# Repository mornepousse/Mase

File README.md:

# Mase
 Custom esp32 mouse.
 
 |index|References|Value|Footprint|Quantity|
 |:-|:--------|:-|:--|:-|
|1| C101, C102, C106, C108, C110    |0.1u|C_0805_2012Metric|5|
|2| C103, C105, C107, C109, C111    |1u|C_0805_2012Metric|5|
|3| C104                            |4.7u|C_0805_2012Metric     |1|
|4| R102, R103, R104                |10k|R_0805_2012Metric|3|
|5| R107, R108, R109                |?|R_0805_2012Metric|3|
|6| R105, R106                      |R_1206|R_0805_2012Metric|2|
|7| R101|39|R_0805_2012Metric|1|
|8| D101, D102|LED_3mm|LED_D3.0mm|2|
|9| U1|ESP32-S3-WROOM-1|ESP32-S3-WROOM-1|1|
|10|U2|PMW3360|PMW3360|1|
|11|U4|	TLV73333PDBV|	SOT-23-5	|1|
|12|U103|	TCR2EF19|	SOT-23-5	|1|
|13|SW1, SW2|	Push_Button|	SW_Hotswap_Kailh_Choc_V1V2_1.00u	|2|
|14|SW101, SW104|	Push_Button|	SW_Micro_Switch	|2|
|15|SW103, SW106|	Push_Button|	SW_Push_1P1T_NO_CK_KSC7xxJ	|2|
|16|SW3|	RotaryEncoder_Switch_MP|	RollerEncoder_Panasonic_EVQWGD001	|1|
|17|	SW102|	Push_Button|Switch_Toggle_SPDT_SubMini	|1|
|18|TP101, TP102, TP103, TP104, TP105, TP106, TP107|TestPoint|TestPoint_Pad_D1.0mm|7|
|19|	H1, H2, H3, H4|	MountingHole|MountingHole_3.2mm_M3|4|
|20|	Brd101|	SSD1306|	128x64OLED	|1|
|21|	J1|	Conn_01x04|	PinHeader_1x04_P2.54mm_Vertical	|1|
|22|	J2|	Conn_02x04_Counter_Clockwise|IDC-Header_2x04_P2.54mm_Vertical|1|
|23|	J101|	Conn_02x03_Counter_Clockwise|	Harwin_Gecko-G125-FVX0605L0X_2x03_P1.25mm_Vertical	|1|

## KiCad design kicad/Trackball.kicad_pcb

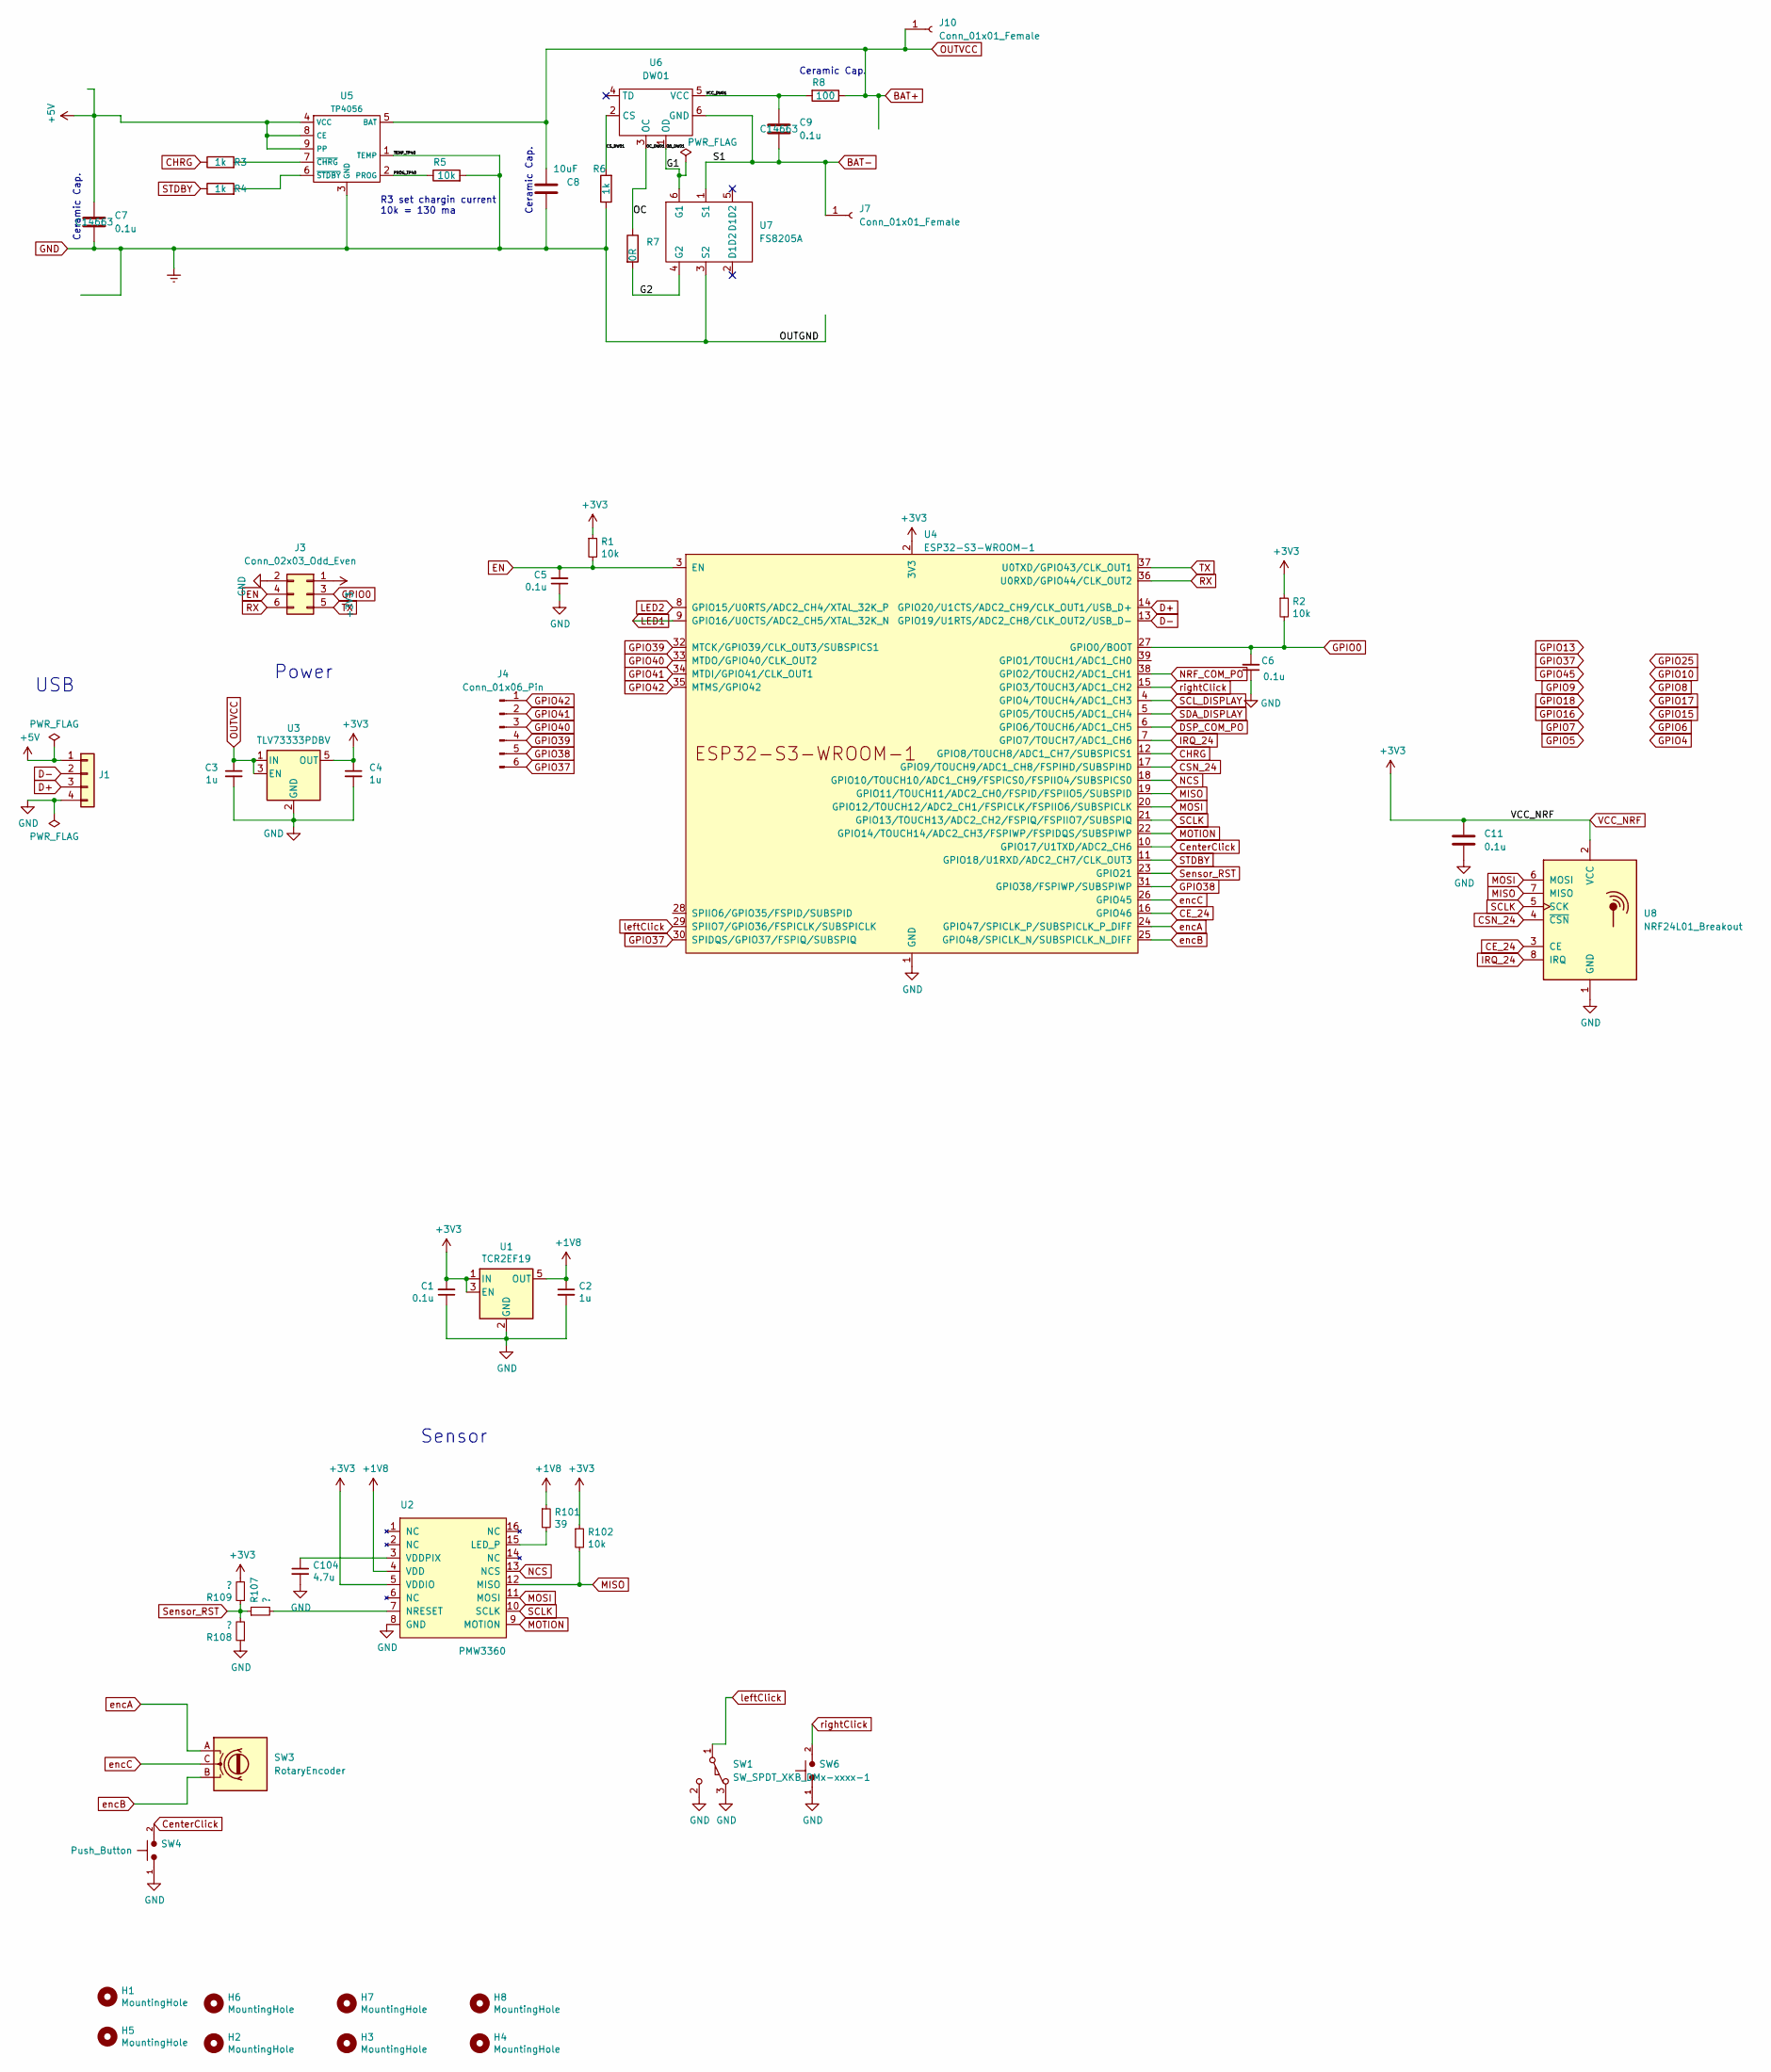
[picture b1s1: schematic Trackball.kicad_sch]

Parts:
C1, C5, C6, C7, C9, C11: 0.1u; C_0805_2012Metric; LCSC C14663
C2: 1u; C_0805_2012Metric; LCSC C15849
C3, C4: 1u; C_0805_2012Metric; LCSC C52923
C8: 10uF; C_0805_2012Metric_Pad1.18x1.45mm_HandSolder
C104: 4.7u; C_0805_2012Metric; LCSC C23733
H1, H2, H3, H4, H5, H6, H7, H8: MountingHole; MountingHole_2.5mm
J1: Conn_01x04; PinHeader_1x04_P2.54mm_Vertical
J3: Conn_02x03_Odd_Even; Harwin_Gecko-G125-FVX0605L0X_2x03_P1.25mm_Vertical
J4: Conn_01x06_Pin; PinHeader_1x06_P2.00mm_Vertical
J7, J10: Conn_01x01_Female; PinSocket_1x01_P2.54mm_Vertical
R1, R2, R102: 10k; R_0805_2012Metric; LCSC C25744
R3, R4, R6: 1k; R_0805_2012Metric
R5: 10k; R_0805_2012Metric
R7: 0R; R_1206_3216Metric_Pad1.30x1.75mm_HandSolder
R8: 100; R_0805_2012Metric_Pad1.20x1.40mm_HandSolder
R101: 39; R_0805_2012Metric; LCSC C25110
R107, R108, R109: ?; R_0805_2012Metric; LCSC C25110
SW1: SW_SPDT_XKB_DMx-xxxx-1; SW_Micro_Switch
SW3: RotaryEncoder; Alps-EC10E1220501
SW4, SW6: Push_Button; SW_Micro_Switch
U1: TCR2EF19; SOT-23-5; LCSC C146366
U2: PMW3360
U3: TLV73333PDBV; SOT-23-5; LCSC C134139
U4: ESP32-S3-WROOM-1
U5: TP4056; SOIC-8-1EP_3.9x4.9mm_P1.27mm_EP2.29x3mm
U6: DW01; SOT-23-6_Handsoldering
U7: FS8205A; SOT-23-6_Handsoldering
U8: NRF24L01_Breakout; NRF24L01-SMD

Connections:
+1V8: C2.1, R101.1, U1.5 (OUT), U2.4 (VDD)
+5V: C7.1, J1.1, U5.4 (VCC), U5.8 (CE), U5.9 (PP)
/CS_DW01: R6.2, U6.2 (CS)
/G1: U6.1 (OD), U7.6 (G1)
/G2: R7.2, U7.4 (G2)
/OC: R7.1, U6.3 (OC)
/PROG_TP40: R5.1, U5.2 (PROG)
/VCC_DW01: C9.1, R8.2, U6.5 (VCC)
BAT+: C3.1, C8.1, J10.1, R8.1, U3.1 (IN), U3.3 (EN), U5.5 (BAT)
BAT-: C9.2, J7.1, U6.6 (GND), U7.1 (S1)
CE_24: U4.16 (GPIO46), U8.3 (CE)
CHRG: R3.1, U4.12 (GPIO8/TOUCH8/ADC1_CH7/SUBSPICS1)
CSN_24: U4.17 (GPIO9/TOUCH9/ADC1_CH8/FSPIHD/SUBSPIHD), U8.4 (~CSN)
CenterClick: SW4.2, U4.10 (GPIO17/U1TXD/ADC2_CH6)
D+: J1.3, U4.14 (GPIO20/U1CTS/ADC2_CH9/CLK_OUT1/USB_D+)
D-: J1.2, U4.13 (GPIO19/U1RTS/ADC2_CH8/CLK_OUT2/USB_D-)
DSP_COM_PO: U4.6 (GPIO6/TOUCH6/ADC1_CH5)
EN: C5.2, J3.4, R1.2, U4.3 (EN)
GND: C1.1, C2.2, C3.2, C4.2, C5.1, C6.1, C7.2, C8.2, C11.2, C104.2, J1.4, J3.2, R5.2, R6.1, R108.1, SW1.2 (B), SW1.3 (C), SW4.1, SW6.1, U1.2 (GND), U2.8 (GND), U3.2 (GND), U4.1 (GND), U4.40 (GND), U4.41 (GND), U5.1 (TEMP), U5.3 (GND), U7.3 (S2), U8.1 (GND)
GPIO0: C6.2, J3.3, R2.2, U4.27 (GPIO0/BOOT)
GPIO37: J4.6, U4.30 (SPIDQS/GPIO37/FSPIQ/SUBSPIQ)
GPIO38: J4.5, U4.31 (GPIO38/FSPIWP/SUBSPIWP)
GPIO39: J4.4, U4.32 (MTCK/GPIO39/CLK_OUT3/SUBSPICS1)
GPIO40: J4.3, U4.33 (MTDO/GPIO40/CLK_OUT2)
GPIO41: J4.2, U4.34 (MTDI/GPIO41/CLK_OUT1)
GPIO42: J4.1, U4.35 (MTMS/GPIO42)
IRQ_24: U4.7 (GPIO7/TOUCH7/ADC1_CH6), U8.8 (IRQ)
LED1: U4.9 (GPIO16/U0CTS/ADC2_CH5/XTAL_32K_N)
LED2: U4.8 (GPIO15/U0RTS/ADC2_CH4/XTAL_32K_P)
MISO: R102.2, U2.12 (MISO), U4.19 (GPIO11/TOUCH11/ADC2_CH0/FSPID/FSPIIO5/S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), U8.7 (MISO)
MOSI: U2.11 (MOSI), U4.20 (GPIO12/TOUCH12/ADC2_CH1/FSPICLK/FSPIIO6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), U8.6 (MOSI)
MOTION: U2.9 (MOTION), U4.22 (GPIO14/TOUCH14/ADC2_CH3/FSPIWP/FSPIDQS/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)
NCS: U2.13 (NCS), U4.18 (GPIO10/TOUCH10/ADC1_CH9/FSPICS0/FSPIIO4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)
NRF_COM_PO: U4.38 (GPIO2/TOUCH2/ADC1_CH1)
unnamed: R101.2, U2.15 (LED_P)
unnamed: R107.2, U2.7 (NRESET)
unnamed: C104.1, U2.3 (VDDPIX)
unnamed: R3.2, U5.7 (~CHRG)
unnamed: R4.2, U5.6 (~STDBY)
RX: J3.6, U4.36 (U0RXD/GPIO44/CLK_OUT2)
SCLK: U2.10 (SCLK), U4.21 (GPIO13/TOUCH13/ADC2_CH2/FSPIQ/FSPIIO7/S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), U8.5 (SCK)
SCL_DISPLAY: U4.4 (GPIO4/TOUCH4/ADC1_CH3)
SDA_DISPLAY: U4.5 (GPIO5/TOUCH5/ADC1_CH4)
STDBY: R4.1, U4.11 (GPIO18/U1RXD/ADC2_CH7/CLK_OUT3)
Sensor_RST: R107.1, R108.2, R109.1, U4.23 (GPIO21)
TX: J3.5, U4.37 (U0TXD/GPIO43/CLK_OUT1)
VCC_NRF: C1.2, C4.1, C11.1, J3.1, R1.1, R2.1, R102.1, R109.2, U1.1 (IN), U1.3 (EN), U2.5 (VDDIO), U3.5 (OUT), U4.2 (3V3), U8.2 (VCC)
encA: SW3.A, U4.24 (GPIO47/SPICLK_P/SUBSPICLK_P_DIFF)
encB: SW3.B, U4.25 (GPIO48/SPICLK_N/SUBSPICLK_N_DIFF)
encC: SW3.C, U4.26 (GPIO45)
leftClick: SW1.1 (A), U4.29 (SPIIO7/GPIO36/FSPICLK/SUBSPICLK)
rightClick: SW6.2, U4.15 (GPIO3/TOUCH3/ADC1_CH2)

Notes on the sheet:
Ceramic Cap.
R3 set chargin current 10k = 130 ma
Power
Sensor
USB

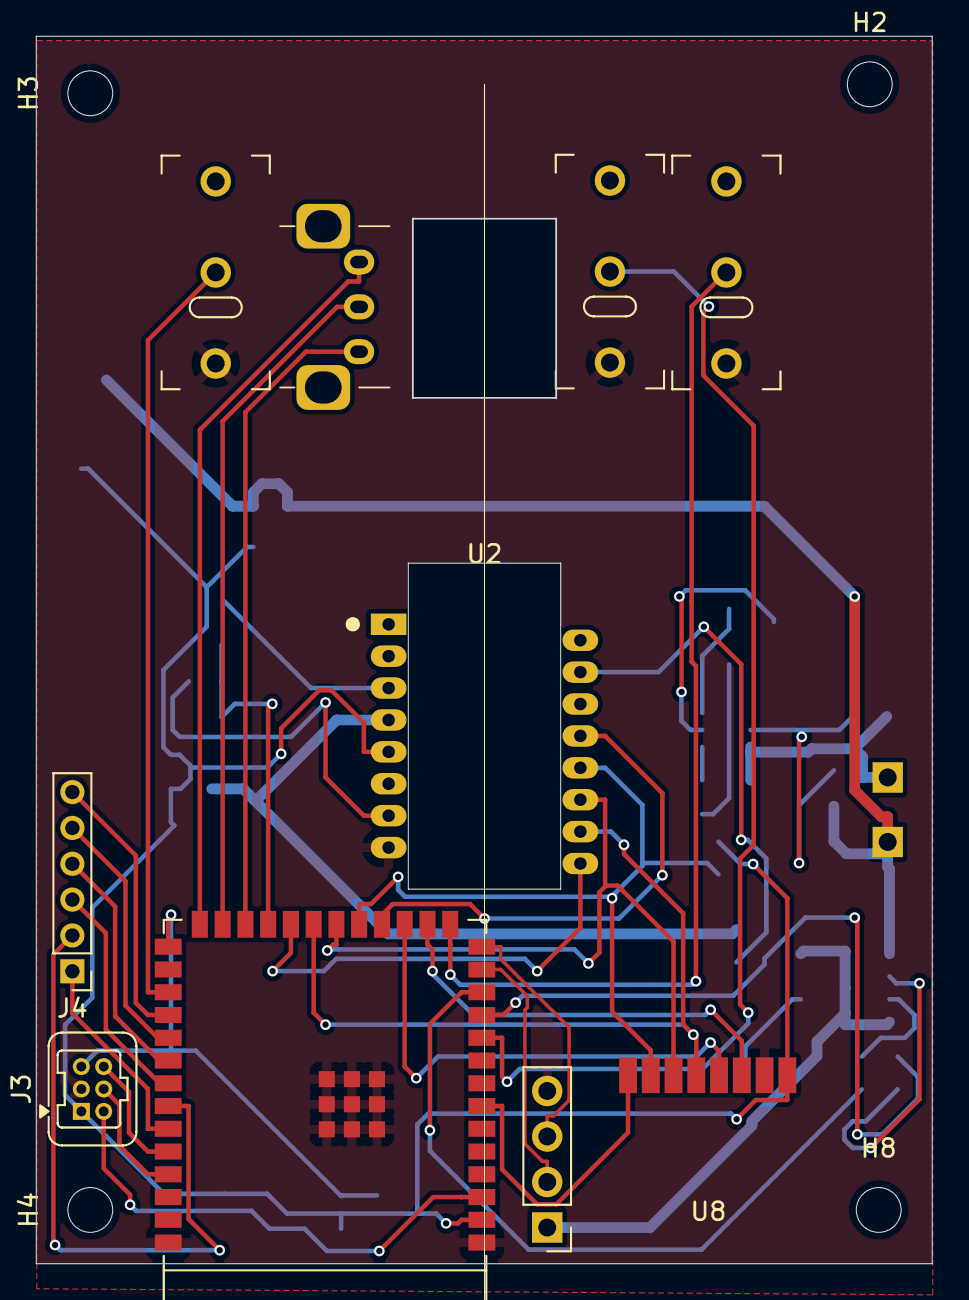
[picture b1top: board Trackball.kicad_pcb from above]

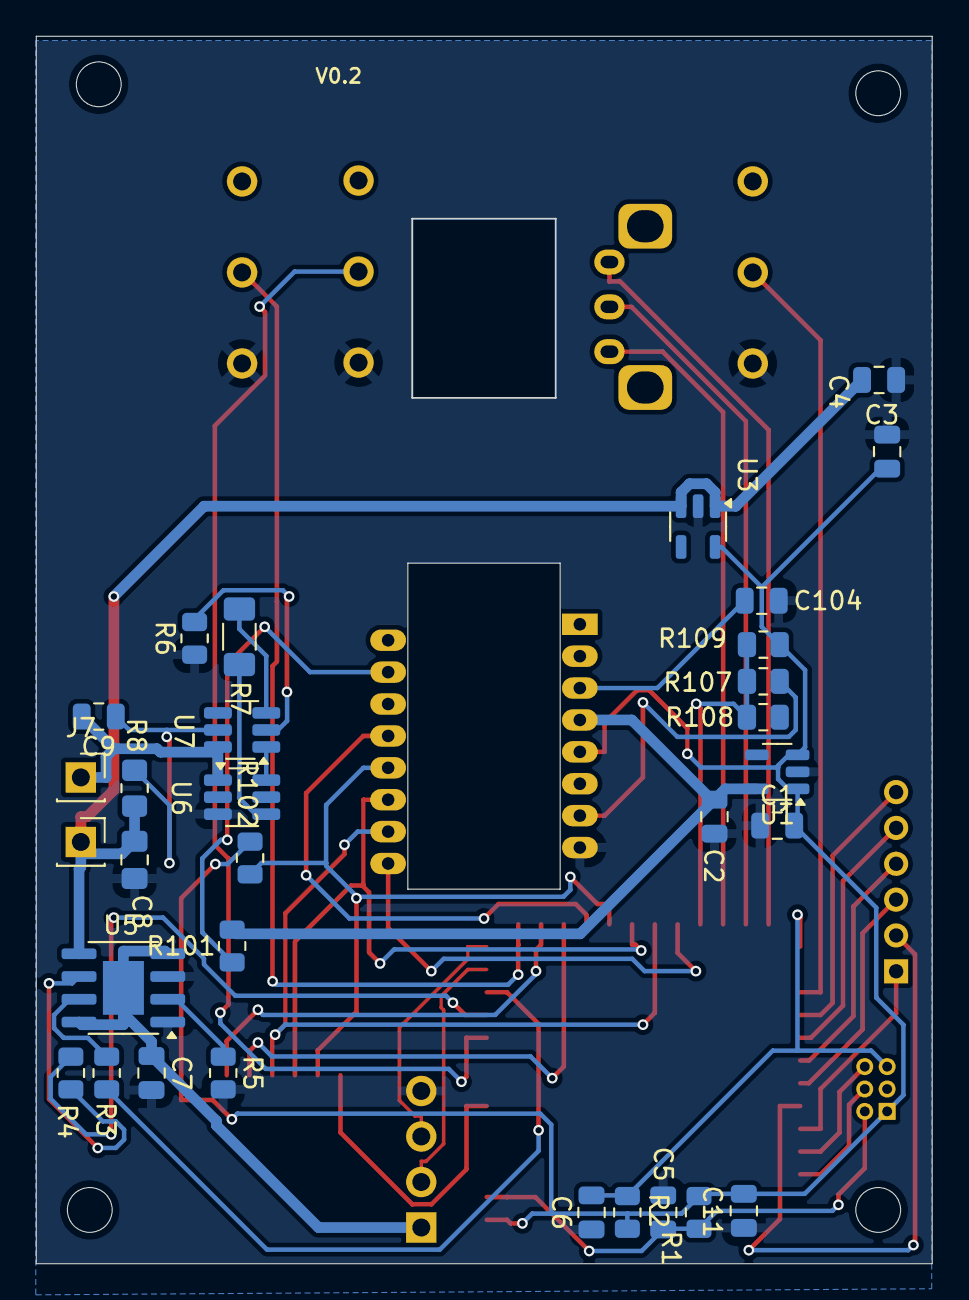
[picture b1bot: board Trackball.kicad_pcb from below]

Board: 2 copper layers, 50.0 x 68.5 mm, 49 parts (31 on the bottom side), 46 nets.

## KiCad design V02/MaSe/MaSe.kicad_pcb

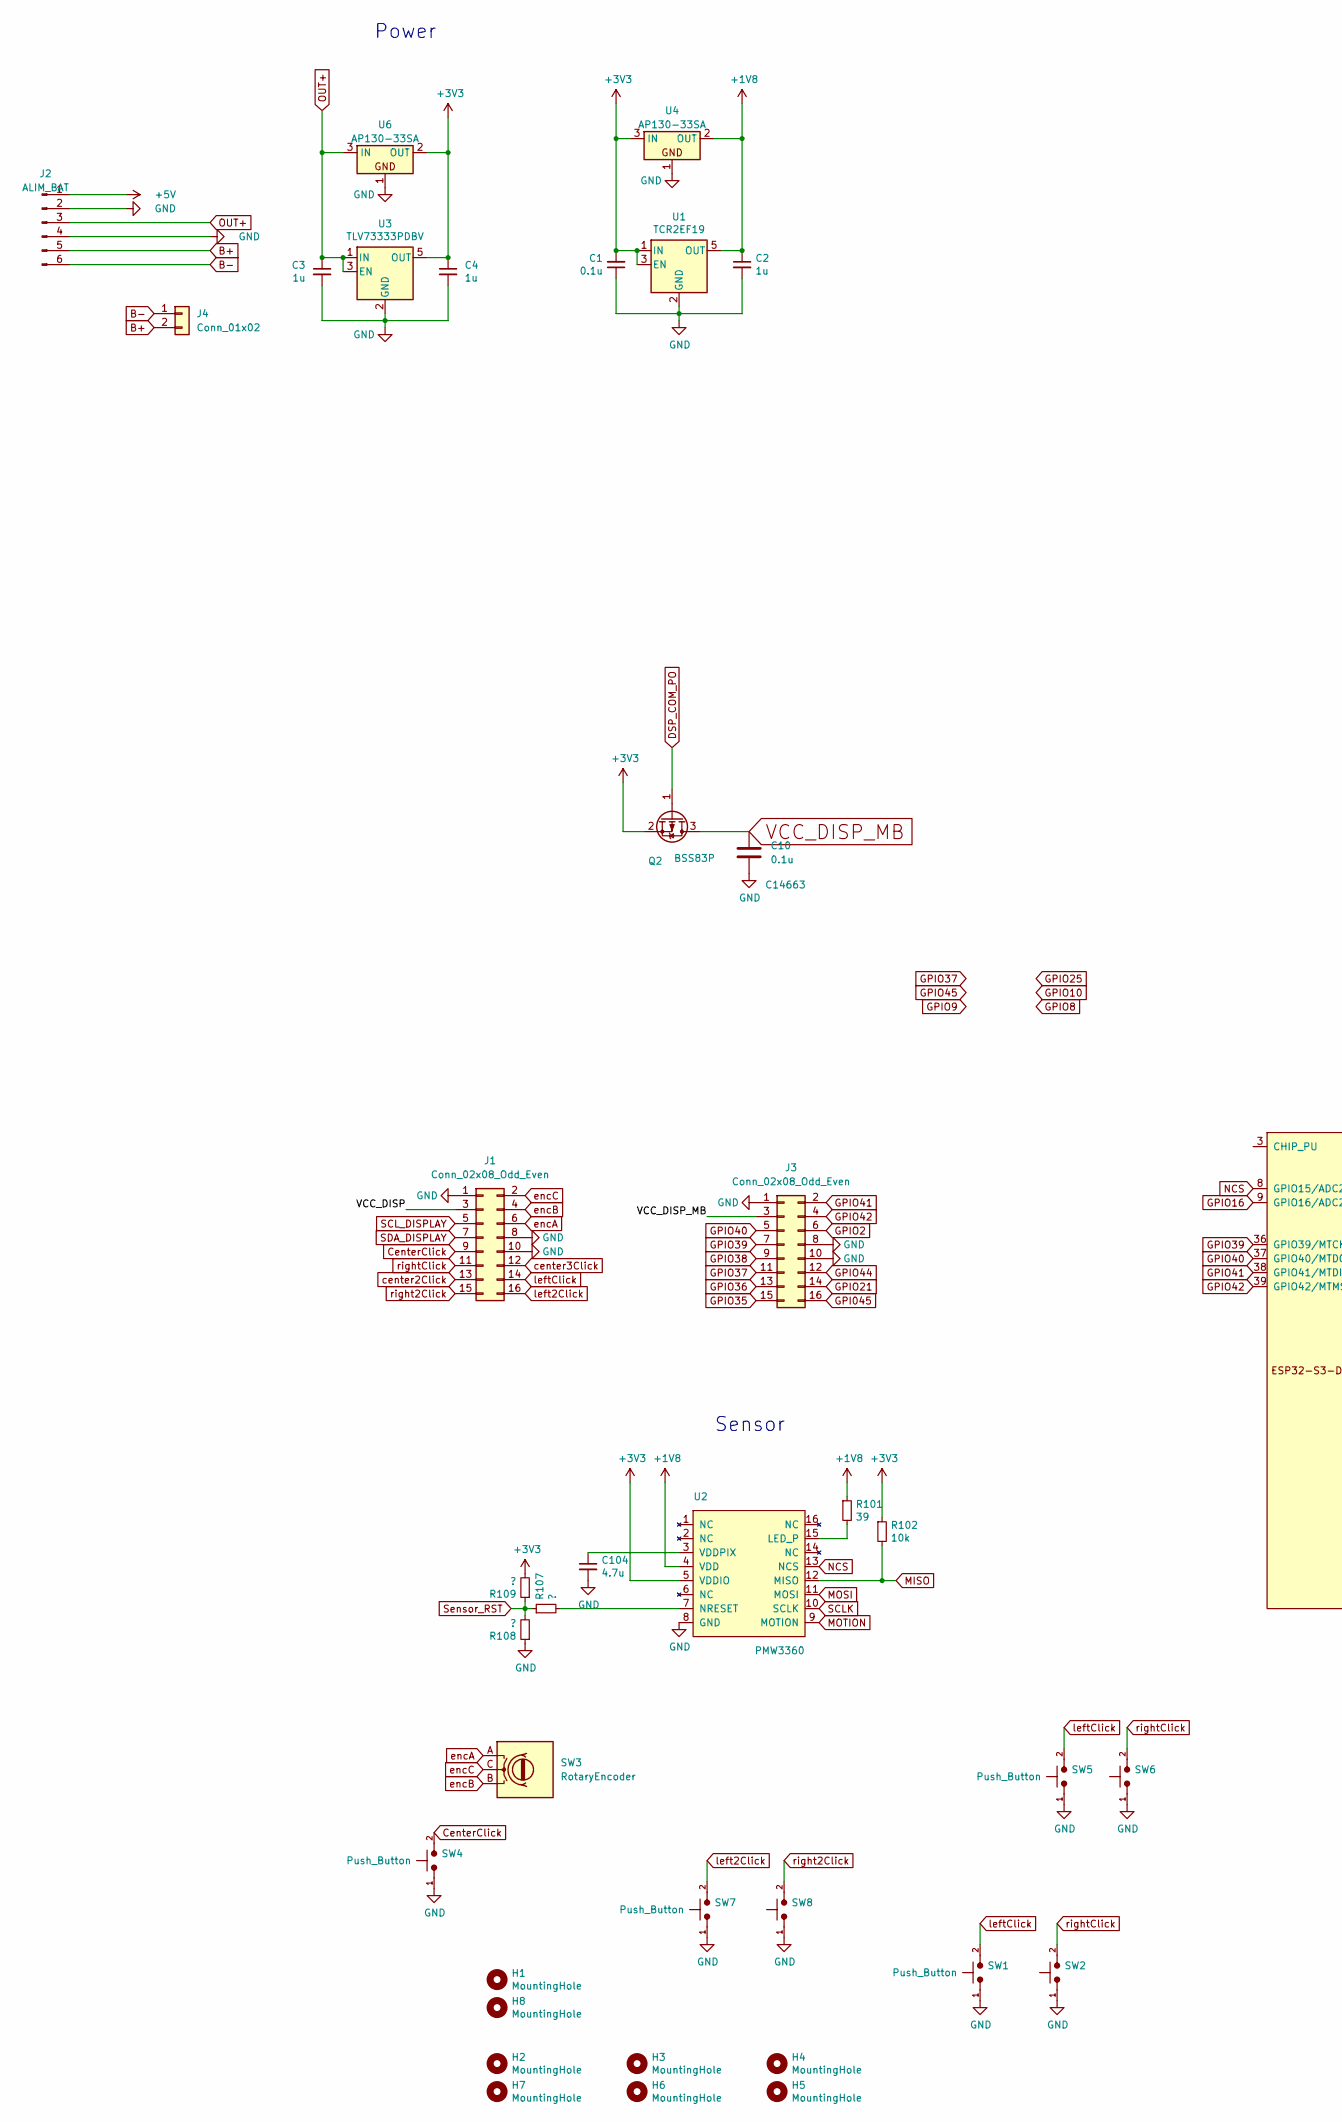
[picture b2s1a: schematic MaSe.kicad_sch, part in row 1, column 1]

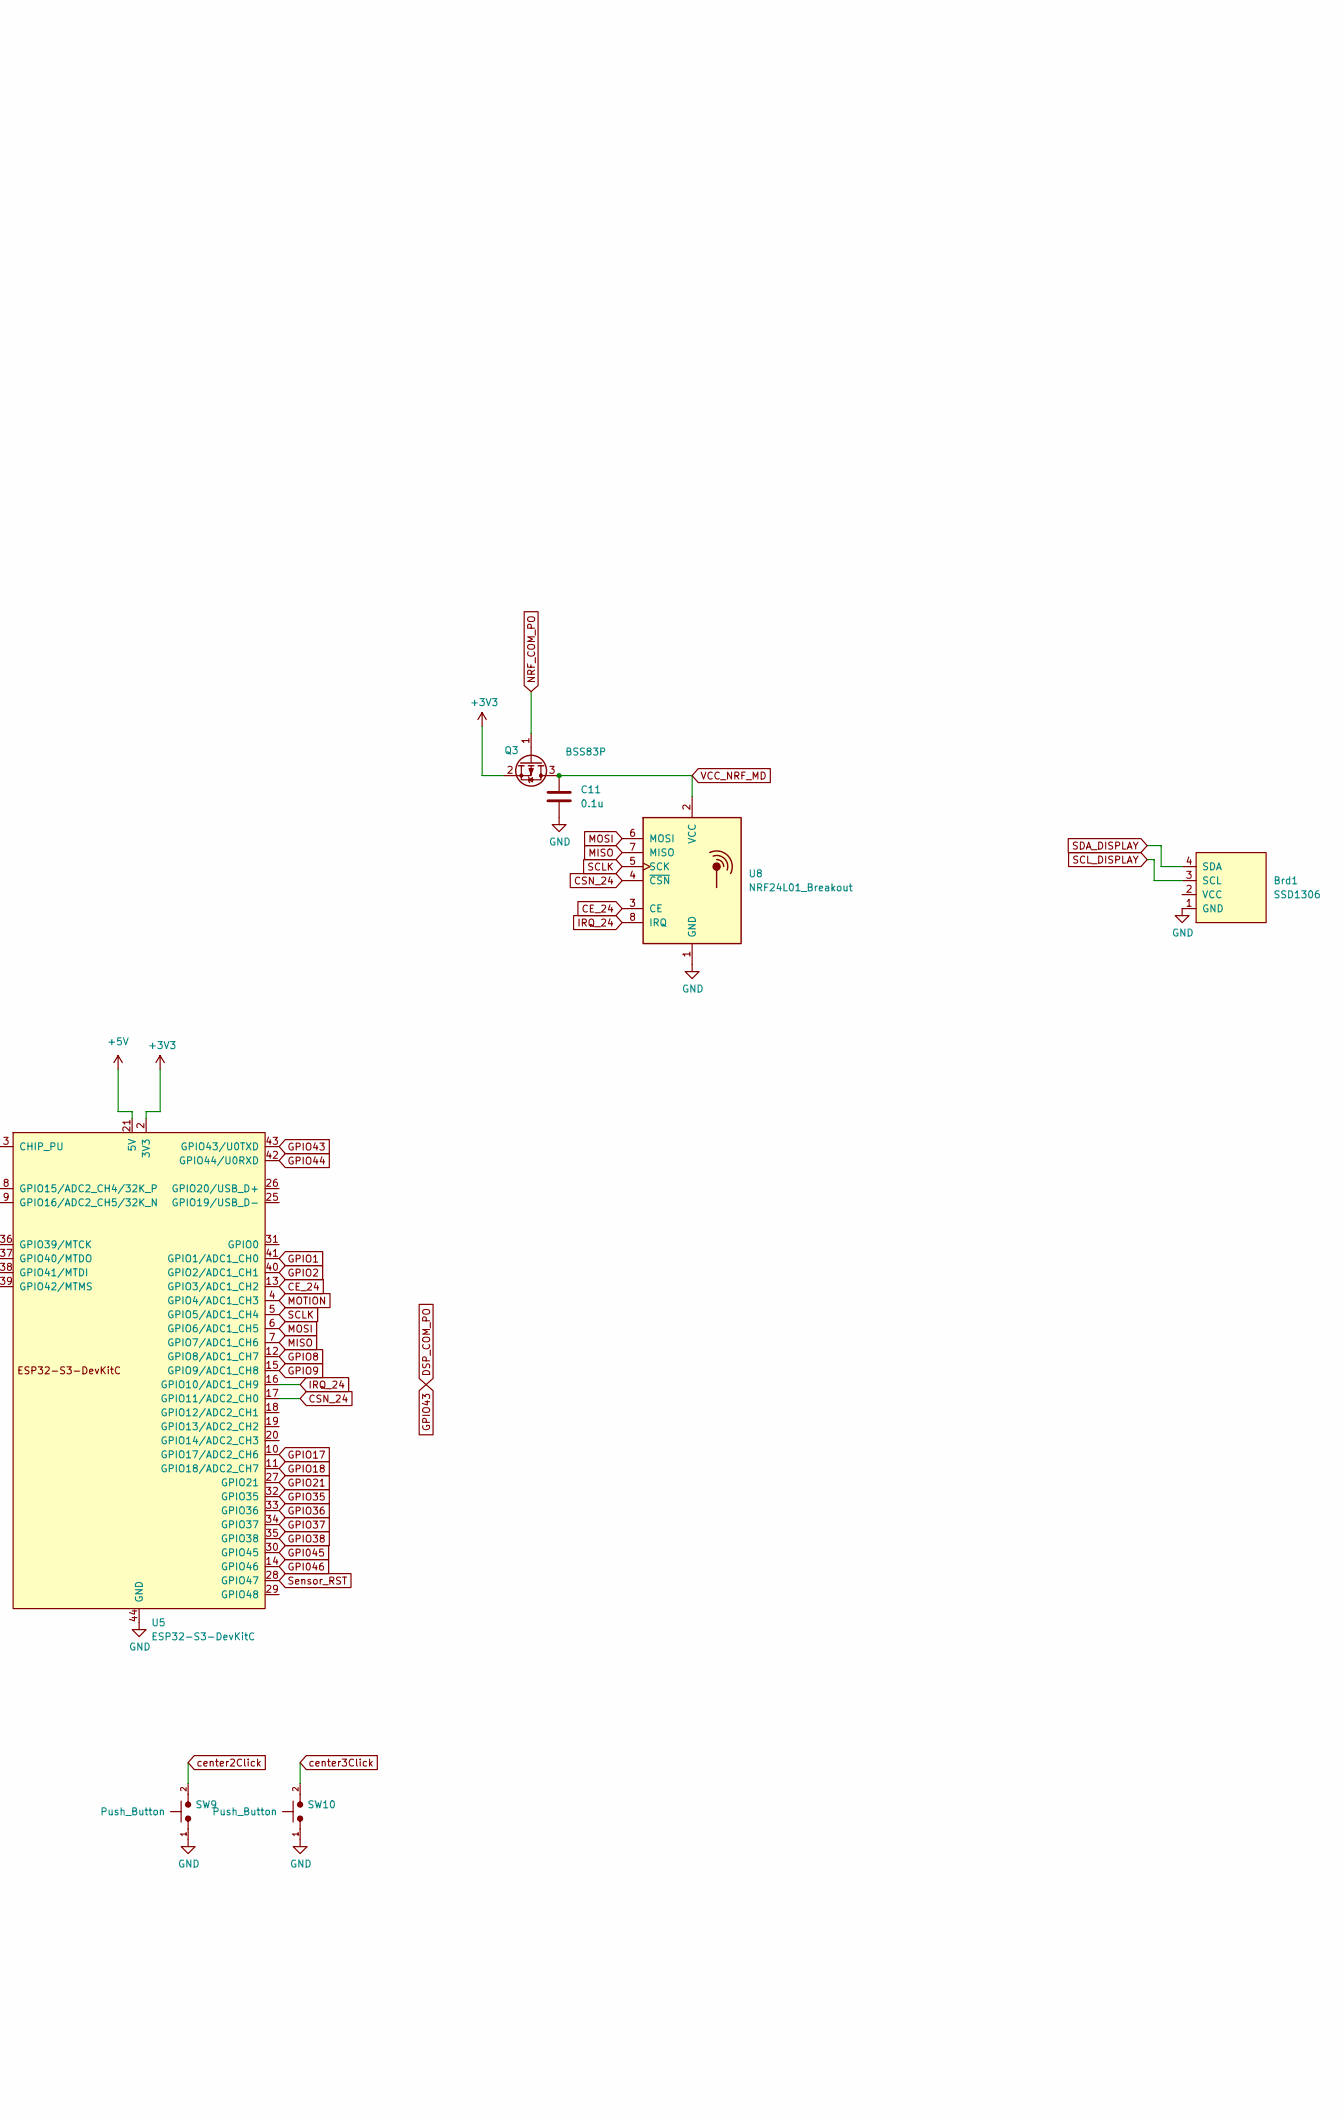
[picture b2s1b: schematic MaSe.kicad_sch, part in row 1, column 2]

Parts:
Brd1: SSD1306; PinHeader_1x04_P2.54mm_Vertical
C1, C10, C11: 0.1u; C_0805_2012Metric; LCSC C14663
C2: 1u; C_0805_2012Metric; LCSC C15849
C3, C4: 1u; C_0805_2012Metric; LCSC C52923
C104: 4.7u; C_0805_2012Metric; LCSC C23733
H1, H2, H3, H4, H5, H6, H7, H8: MountingHole; MountingHole_2.2mm_M2_ISO14580
J1, J3: Conn_02x08_Odd_Even; PinHeader_2x08_P1.27mm_Vertical
J2: ALIM_BAT; TP4056-18650
J4: Conn_01x02; PinHeader_1x02_P2.54mm_Vertical
Q2, Q3: BSS83P; SOT-23
R101: 39; R_0805_2012Metric; LCSC C25110
R102: 10k; R_0805_2012Metric; LCSC C25744
R107, R108, R109: ?; R_0805_2012Metric; LCSC C25110
SW1, SW2, SW7, SW8: Push_Button; SW_Hotswap_Kailh_Choc_V1V2_1.00u
SW3: RotaryEncoder; Alps-EC10E1220501
SW4, SW5, SW6: Push_Button; SW_Micro_Switch
SW9, SW10: Push_Button; SW_PUSH_6mm
U1: TCR2EF19; SOT-23-5; LCSC C146366
U2: PMW3360
U3: TLV73333PDBV; SOT-23-5; LCSC C134139
U4, U6: AP130-33SA; SOT-23
U5: ESP32-S3-DevKitC
U8: NRF24L01_Breakout; nRF24L01_Breakout

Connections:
+1V8: C2.1, R101.1, U1.5 (OUT), U2.4 (VDD), U4.2 (OUT)
+3V3: C1.2, C4.1, Q2.2 (S), Q3.2 (S), R102.1, R109.2, U1.1 (IN), U1.3 (EN), U2.5 (VDDIO), U3.5 (OUT), U4.3 (IN), U5.1 (3V3), U5.2 (3V3), U6.2 (OUT)
+5V: J2.1, U5.21 (5V)
/VCC_DISP: J1.3
B+: J2.5, J4.2
B-: J2.6, J4.1
CE_24: U5.13 (GPIO3/ADC1_CH2), U8.3 (CE)
CSN_24: U5.17 (GPIO11/ADC2_CH0), U8.4 (~CSN)
CenterClick: J1.9, SW4.2
DSP_COM_PO: Q2.1 (G), U5.43 (GPIO43/U0TXD)
GND: Brd1.1 (GND), C1.1, C2.2, C3.2, C4.2, C10.2, C11.2, C104.2, J1.1, J1.8, J1.10, J2.2, J2.4, J3.1, J3.8, J3.10, R108.1, SW1.1, SW2.1, SW4.1, SW5.1, SW6.1, SW7.1, SW8.1, SW9.1, SW10.1, U1.2 (GND), U2.8 (GND), U3.2 (GND), U4.1, U5.22 (GND), U5.23 (GND), U5.24 (GND), U5.44 (GND), U6.1, U8.1 (GND)
GPI045: J3.16, U5.30 (GPIO45)
GPI046: U5.14 (GPIO46)
GPIO1: U5.41 (GPIO1/ADC1_CH0)
GPIO2: J3.6, U5.40 (GPIO2/ADC1_CH1)
GPIO8: U5.12 (GPIO8/ADC1_CH7)
GPIO9: U5.15 (GPIO9/ADC1_CH8)
GPIO16: U5.9 (GPIO16/ADC2_CH5/32K_N)
GPIO17: U5.10 (GPIO17/ADC2_CH6)
GPIO18: U5.11 (GPIO18/ADC2_CH7)
GPIO21: J3.14, U5.27 (GPIO21)
GPIO35: J3.15, U5.32 (GPIO35)
GPIO36: J3.13, U5.33 (GPIO36)
GPIO37: J3.11, U5.34 (GPIO37)
GPIO38: J3.9, U5.35 (GPIO38)
GPIO39: J3.7, U5.36 (GPIO39/MTCK)
GPIO40: J3.5, U5.37 (GPIO40/MTDO)
GPIO41: J3.2, U5.38 (GPIO41/MTDI)
GPIO42: J3.4, U5.39 (GPIO42/MTMS)
GPIO44: J3.12, U5.42 (GPIO44/U0RXD)
IRQ_24: U5.16 (GPIO10/ADC1_CH9), U8.8 (IRQ)
MISO: R102.2, U2.12 (MISO), U5.7 (GPIO7/ADC1_CH6), U8.7 (MISO)
MOSI: U2.11 (MOSI), U5.6 (GPIO6/ADC1_CH5), U8.6 (MOSI)
MOTION: U2.9 (MOTION), U5.4 (GPIO4/ADC1_CH3)
NCS: U2.13 (NCS), U5.8 (GPIO15/ADC2_CH4/32K_P)
NRF_COM_PO: Q3.1 (G)
unnamed: R101.2, U2.15 (LED_P)
unnamed: R107.2, U2.7 (NRESET)
unnamed: C104.1, U2.3 (VDDPIX)
OUT+: C3.1, J2.3, U3.1 (IN), U3.3 (EN), U6.3 (IN)
SCLK: U2.10 (SCLK), U5.5 (GPIO5/ADC1_CH4), U8.5 (SCK)
SCL_DISPLAY: Brd1.3 (SCL), J1.5
SDA_DISPLAY: Brd1.4 (SDA), J1.7
Sensor_RST: R107.1, R108.2, R109.1, U5.28 (GPIO47)
VCC_DISP_MB: C10.1, J3.3, Q2.3 (D)
VCC_NRF_MD: C11.1, Q3.3 (D), U8.2 (VCC)
center2Click: J1.13, SW9.2
center3Click: J1.12, SW10.2
encA: J1.6, SW3.A
encB: J1.4, SW3.B
encC: J1.2, SW3.C
left2Click: J1.16, SW7.2
leftClick: J1.14, SW1.2, SW5.2
right2Click: J1.15, SW8.2
rightClick: J1.11, SW2.2, SW6.2

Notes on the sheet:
Power
Sensor

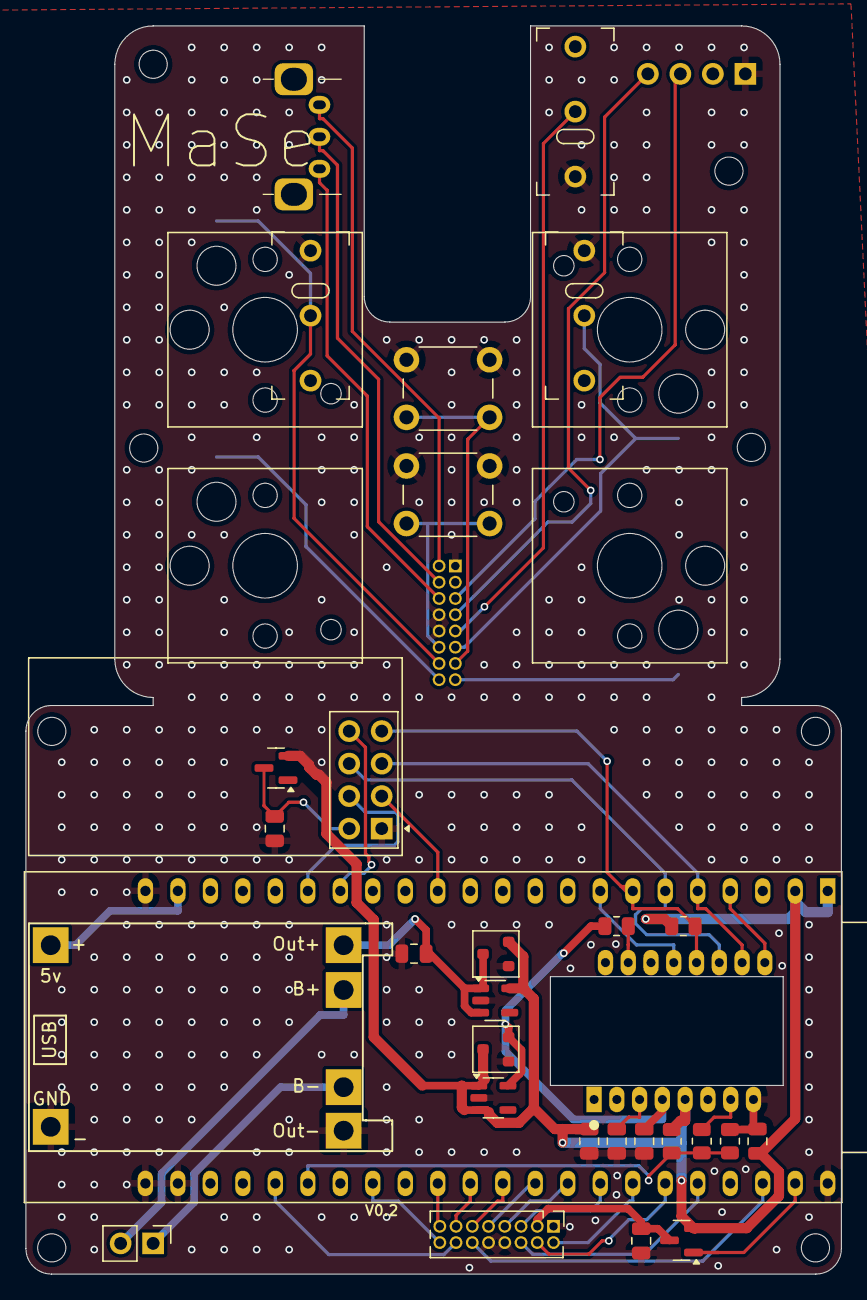
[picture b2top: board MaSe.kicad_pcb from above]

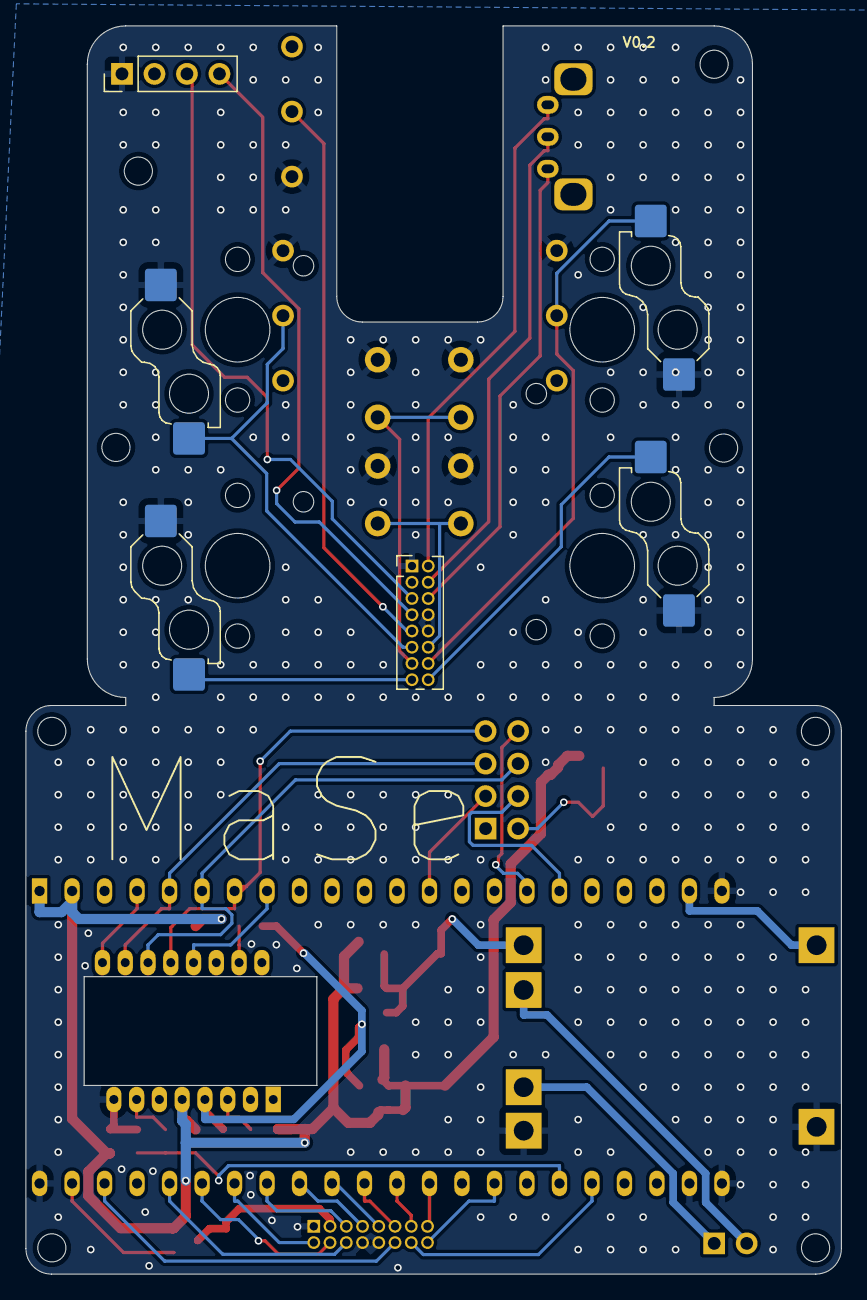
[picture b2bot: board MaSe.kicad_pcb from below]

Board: 2 copper layers, 63.8 x 97.6 mm, 44 parts (2 on the bottom side), 46 nets.
